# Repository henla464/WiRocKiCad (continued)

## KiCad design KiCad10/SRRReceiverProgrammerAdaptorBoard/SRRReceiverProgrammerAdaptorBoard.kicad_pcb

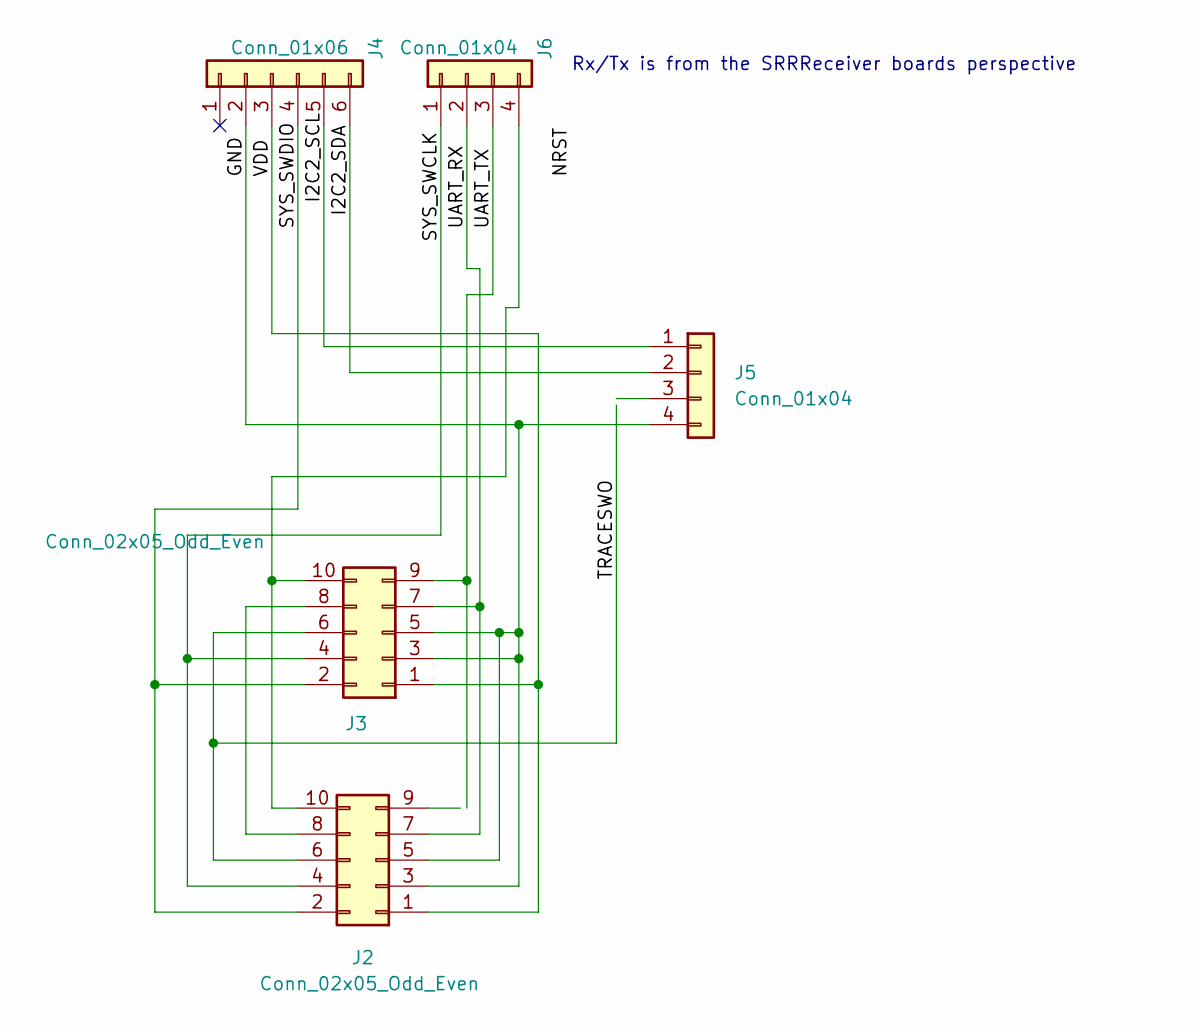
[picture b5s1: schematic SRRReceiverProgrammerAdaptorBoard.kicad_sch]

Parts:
J2, J3: Conn_02x05_Odd_Even; PinHeader_2x05_P1.27mm_Vertical
J4: Conn_01x06; PinHeader_1x06_P1.27mm_Horizontal
J5: Conn_01x04; PinHeader_1x04_P2.54mm_Vertical
J6: Conn_01x04; PinHeader_1x04_P1.27mm_Horizontal

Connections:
/GND: J2.3, J2.5, J3.3, J3.5, J4.2, J5.4
/I2C2_SCL: J4.5, J5.1
/I2C2_SDA: J4.6, J5.2
/SYS_SWCLK: J2.4, J3.4, J6.1
/SYS_SWDIO: J2.2, J3.2, J4.4
/TRACESWO: J2.6, J3.6
/UART_RX: J2.7, J3.7, J6.2
/UART_TX: J3.9, J6.3
/VDD: J2.1, J3.1, J4.3
unnamed: J2.8, J3.8
unnamed: J2.10, J3.10, J6.4

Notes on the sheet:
Rx/Tx is from the SRRReceiver boards perspective

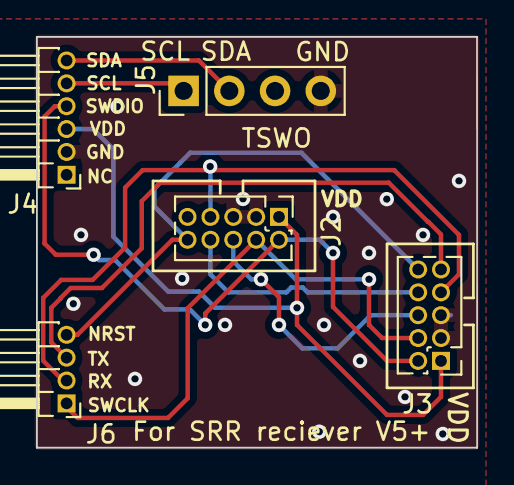
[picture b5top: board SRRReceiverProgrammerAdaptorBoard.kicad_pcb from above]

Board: 2 copper layers, 24.5 x 22.8 mm, 5 parts (0 on the bottom side), 11 nets.

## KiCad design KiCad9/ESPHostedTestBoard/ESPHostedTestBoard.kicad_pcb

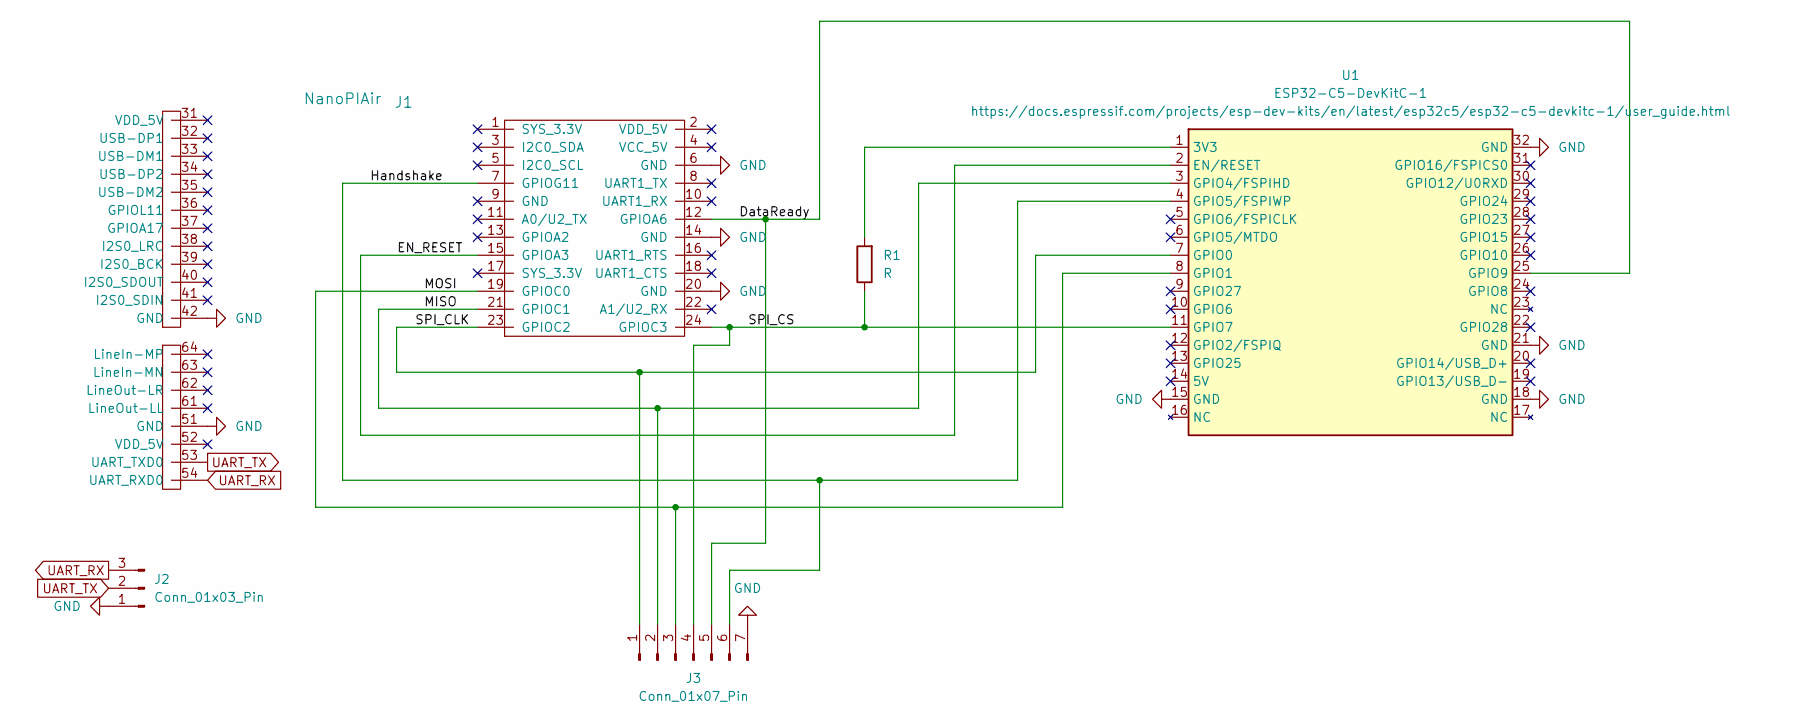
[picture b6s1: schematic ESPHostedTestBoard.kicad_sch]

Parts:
J1: NanoPIAir; NanoPiNeoAirAllPins
J2: Conn_01x03_Pin; PinHeader_1x03_P2.54mm_Vertical
J3: Conn_01x07_Pin; PinHeader_1x07_P2.54mm_Vertical
R1: R; R_0805_2012Metric
U1: ESP32-C5-DevKitC-1

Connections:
/DataReady: J1.12 (GPIOA6), J3.5, U1.25 (GPIO9)
/EN_RESET: J1.15 (GPIOA3), U1.2 (EN/RESET)
/Handshake: J1.7 (GPIOG11), J3.6, U1.4 (GPIO5/FSPIWP)
/MISO: J1.21 (GPIOC1), J3.2, U1.3 (GPIO4/FSPIHD)
/MOSI: J1.19 (GPIOC0), J3.3, U1.8 (GPIO1)
/SPI_CLK: J1.23 (GPIOC2), J3.1, U1.7 (GPIO0)
/SPI_CS: J1.24 (GPIOC3), J3.4, R1.1, U1.11 (GPIO7)
GND: J1.6 (GND), J1.14 (GND), J1.20 (GND), J1.42 (GND), J1.51 (GND), J2.1, J3.7, U1.15 (GND), U1.18 (GND), U1.21 (GND), U1.32 (GND)
unnamed: R1.2, U1.1 (3V3)
UART_RX: J1.54 (UART_RXD0), J2.3
UART_TX: J1.53 (UART_TXD0), J2.2

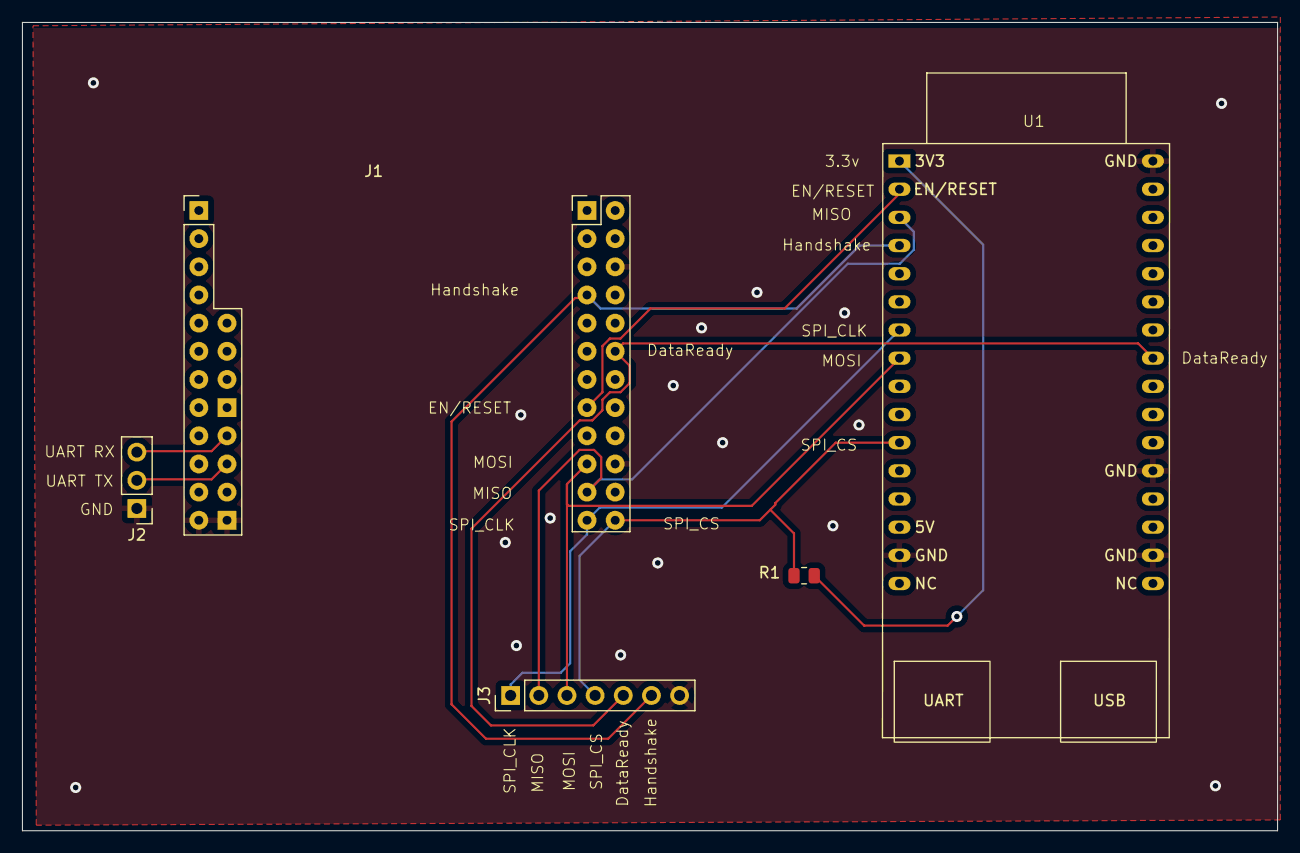
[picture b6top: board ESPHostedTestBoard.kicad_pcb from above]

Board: 2 copper layers, 113.2 x 72.9 mm, 5 parts (0 on the bottom side), 11 nets.

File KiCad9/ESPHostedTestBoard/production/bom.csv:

Designator,Footprint,Quantity,Value,LCSC Part #
J1,NanoPiNeoAirAllPins,1,NanoPIAir,
J2,PinHeader_1x03_P2.54mm_Vertical,1,Conn_01x03_Pin,
J3,PinHeader_1x07_P2.54mm_Vertical,1,Conn_01x07_Pin,
R1,0805,1,R,
U1,ESP32-C5-DevKitC-1,1,ESP32-C5-DevKitC-1,

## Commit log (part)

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2022-01-19 add KiCad6 versions
2022-09-06 add USBRadio etc
2023-06-16 add KiCad7
2023-11-12 diverse SRR etc
2024-07-03 wiroc v8 layout work
2024-07-08 more routing of v8
2024-07-08 more v8 routing
2025-09-28 sbc version etc
2025-10-19 more routing of WiRoc_v8, upgraded USBConnectorPlate to v9 and with ferrit beads, added an ESPHosted testboard
2025-10-19 fill exclusion for emmc, adjust lengths emmc
2025-10-31 Change SRRReceiver pins,
2025-10-31 add bom
2025-10-31 add oshw logo
2025-11-16 change tracewidth for mem, add nettie for better length calculation
2025-11-17 adjustments length and width of traces
2025-11-21 add rst to wifi board
2025-11-21 add esp32-c5-wroom to library
2025-11-22 add esp32hosted-c5 board
2025-11-25 change to 10uF in pdn, vdd-dram area to south caps, remove varistor, etc
2025-11-25 cleanup
2025-11-26 save point for fix to layer issues in6
2025-11-28 shorten spi meander, dataready/handshake shouldn't be length matched to spi. Move eMMC-cmd pullup to processor via. Make meanders more spacious.
2025-11-29 many small changes, change eMMC
2025-12-02 change gnd planes to 0.12 clearance and 0.09 minimum width, move some vias create path inbetween
2025-12-02 remove lock files
2025-12-02 more clearance adjustments for vias
2025-12-04 add 3d of wifiboard
2025-12-13 remove ignored production dir
2026-01-02 change hole size to smaller, to better fit the pins
2026-01-02 change to use smaller pin holes
2026-01-02 changed some vias to make them smaller like the others
2026-01-03 make holes smaller to fit pins better
2026-03-19 add ethernet etc
2026-03-29 KiCad10
2026-03-29 diverse
2026-04-02 Remove .history folders and ignore them
2026-04-02 remove lck
2026-04-02 kicad10 and .gitignore lck history
2026-04-11 add logo, improve layout
2026-04-11 remove test project
